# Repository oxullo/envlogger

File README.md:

# ENVLogger

Versatile hardware for logging/controlling environmental conditions.

Currently equipping:

* 2x Type-K Thermocouples EMF to digital converters
* Local Bosch-Sensortec BME680 environmental sensor
	* Temperature
	* Humidity
	* Atmospheric pressure
	* Volatile organic compounds
* 2x generic I/Os for additional 1-wire sensors (eg: DS1820B)
* 2x open-drain outputs
* 128x32, backlit FSTN LCD display
* Two buttons

## The article

Most of the information regarding this device can be found here: https://www.xul.it/blog/index.php/2020/05/16/envlogger-v1-rev-a/

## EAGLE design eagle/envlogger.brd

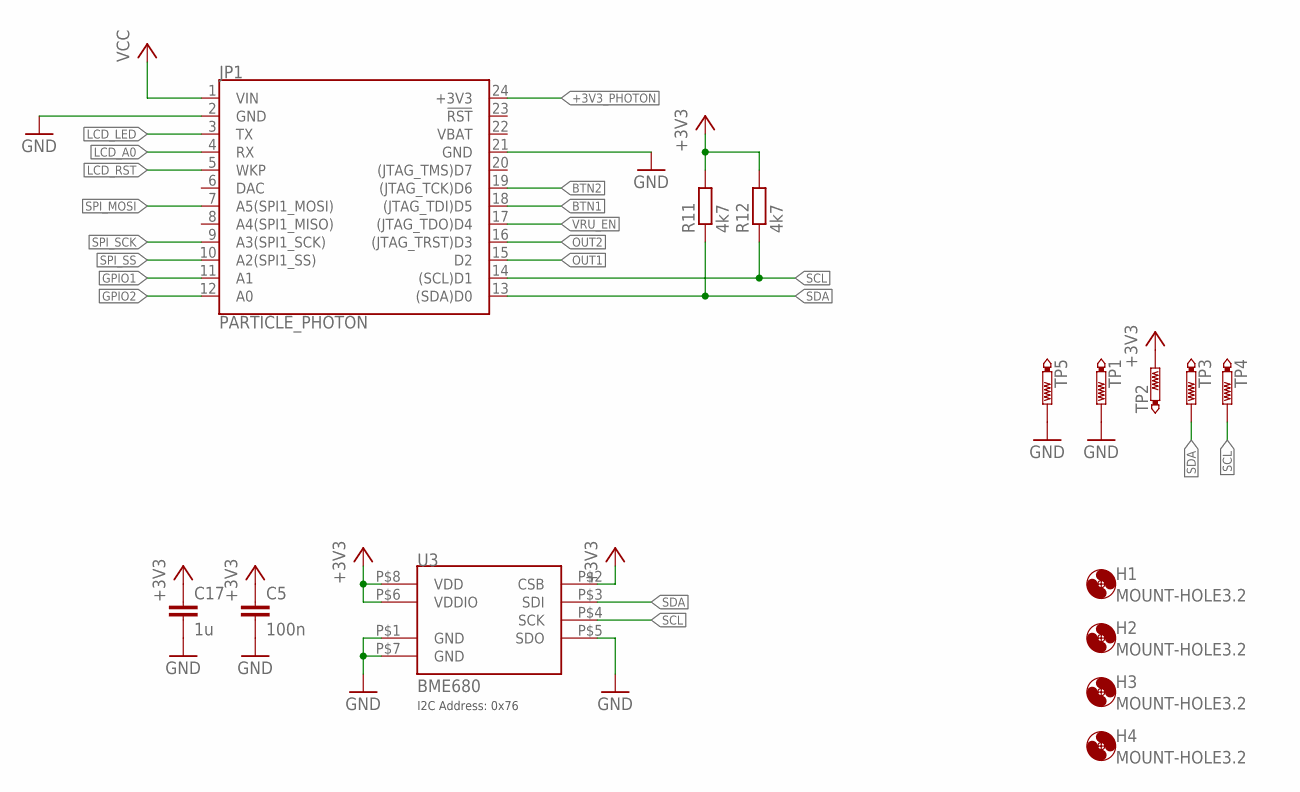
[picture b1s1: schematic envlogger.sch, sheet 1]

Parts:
C5: 100n; C0603
C17: 1u; C0603
H1, H2, H3, H4: MOUNT-HOLE3.2; 3,2
JP1: PARTICLE_PHOTON
R11, R12: 4k7; R0603
TP1, TP2, TP3, TP4: PTR1B1,27; B1,27
TP5: PTR1PAD1-13; P1-13
U3: BME680

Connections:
+3V3: C5.1, C17.1, R11.2, R12.2, TP2.TP, U3.P$2 (CSB), U3.P$6 (VDDIO), U3.P$8 (VDD); also elsewhere on the board
+3V3_PHOTON: JP1.24 (+3V3)
BTN1: JP1.18 ((JTAG_TDI)D5); also elsewhere on the board
BTN2: JP1.19 ((JTAG_TCK)D6); also elsewhere on the board
GND: C5.2, C17.2, JP1.2 (GND), JP1.21 (GND), TP1.TP, TP5.TP, U3.P$1 (GND), U3.P$5 (SDO), U3.P$7 (GND); also elsewhere on the board
GPIO1: JP1.11 (A1); also elsewhere on the board
GPIO2: JP1.12 (A0); also elsewhere on the board
LCD_A0: JP1.4 (RX); also elsewhere on the board
LCD_LED: JP1.3 (TX); also elsewhere on the board
LCD_RST: JP1.5 (WKP); also elsewhere on the board
OUT1: JP1.15 (D2); also elsewhere on the board
OUT2: JP1.16 ((JTAG_TRST)D3); also elsewhere on the board
SCL: JP1.14 ((SCL)D1), R12.1, TP4.TP, U3.P$4 (SCK); also elsewhere on the board
SDA: JP1.13 ((SDA)D0), R11.1, TP3.TP, U3.P$3 (SDI); also elsewhere on the board
SPI_MOSI: JP1.7 (A5(SPI1_MOSI)); also elsewhere on the board
SPI_SCK: JP1.9 (A3(SPI1_SCK)); also elsewhere on the board
SPI_SS: JP1.10 (A2(SPI1_SS)); also elsewhere on the board
VBAT: JP1.22 (VBAT)
VCC: JP1.1 (VIN); also elsewhere on the board
VRU_EN: JP1.17 ((JTAG_TDO)D4); also elsewhere on the board

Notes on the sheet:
I2C Address: 0x76

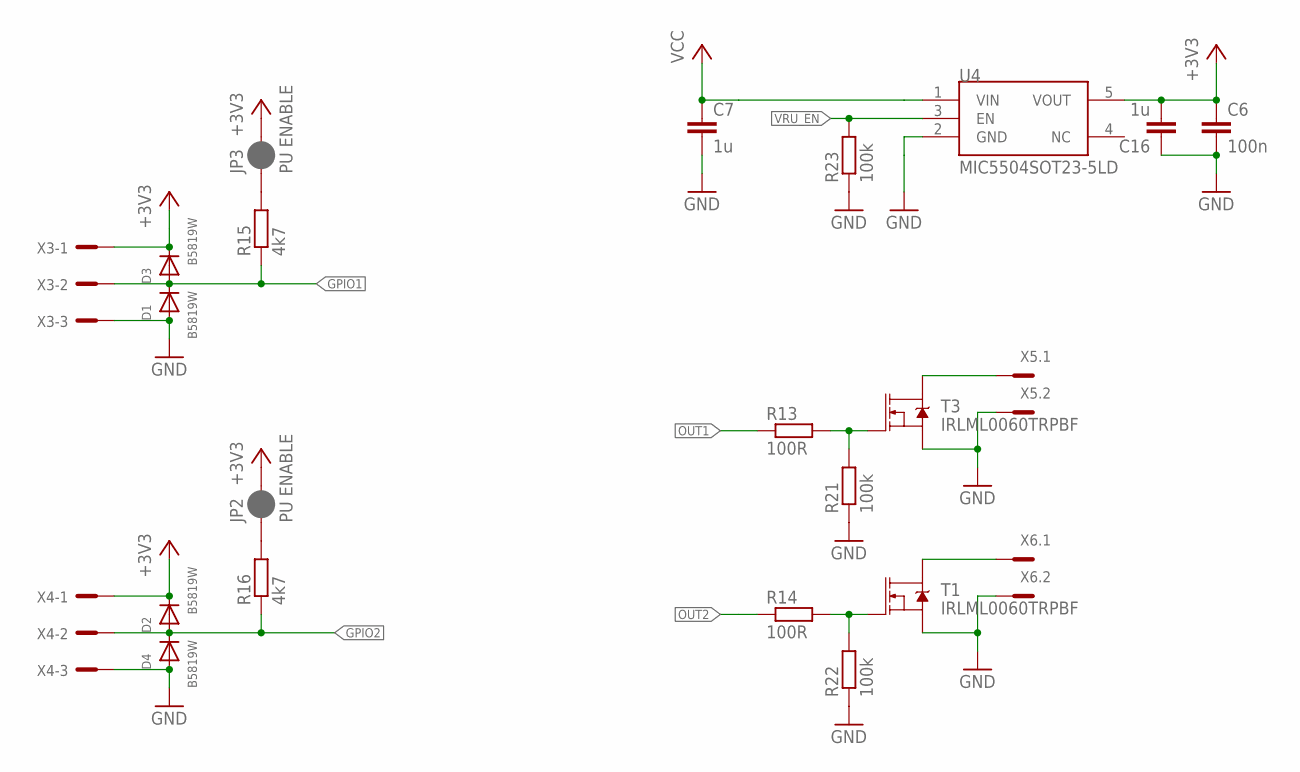
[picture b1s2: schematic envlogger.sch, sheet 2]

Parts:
C6: 100n; C0603
C7, C16: 1u; C0603
D1, D2, D3, D4: B5819W; SOD-123
JP2, JP3: PU ENABLE; SMT-JUMPER_2_NC_PASTE_SILK
R13, R14: 100R; R0603
R15, R16: 4k7; R0603
R21, R22, R23: 100k; R0603
T1, T3: IRLML0060TRPBF; SOT95P237X112-3N
U4: MIC5504SOT23-5LD; SOT95P280X145-5
X3, X4: MCV_05/3-G-2,5; MC3
X5, X6: MC2

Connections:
+3V3: C6.1, C16.2, D2.C, D3.C, JP2.2, JP3.2, U4.5 (VOUT), X3.1, X4.1; also elsewhere on the board
GND: C6.2, C7.2, C16.1, D1.A, D4.A, R21.1, R22.1, R23.1, T1.2 (S), T3.2 (S), U4.2 (GND), X3.3, X4.3, X5.2, X6.2; also elsewhere on the board
GPIO1: D1.C, D3.A, R15.1, X3.2; also elsewhere on the board
GPIO2: D2.A, D4.C, R16.1, X4.2; also elsewhere on the board
unnamed: T3.3 (D), X5.1
unnamed: R13.2, R21.2, T3.1 (G)
unnamed: T1.3 (D), X6.1
unnamed: R14.2, R22.2, T1.1 (G)
unnamed: JP2.1, R16.2
unnamed: JP3.1, R15.2
OUT1: R13.1; also elsewhere on the board
OUT2: R14.1; also elsewhere on the board
VCC: C7.1, U4.1 (VIN); also elsewhere on the board
VRU_EN: R23.2, U4.3 (EN); also elsewhere on the board

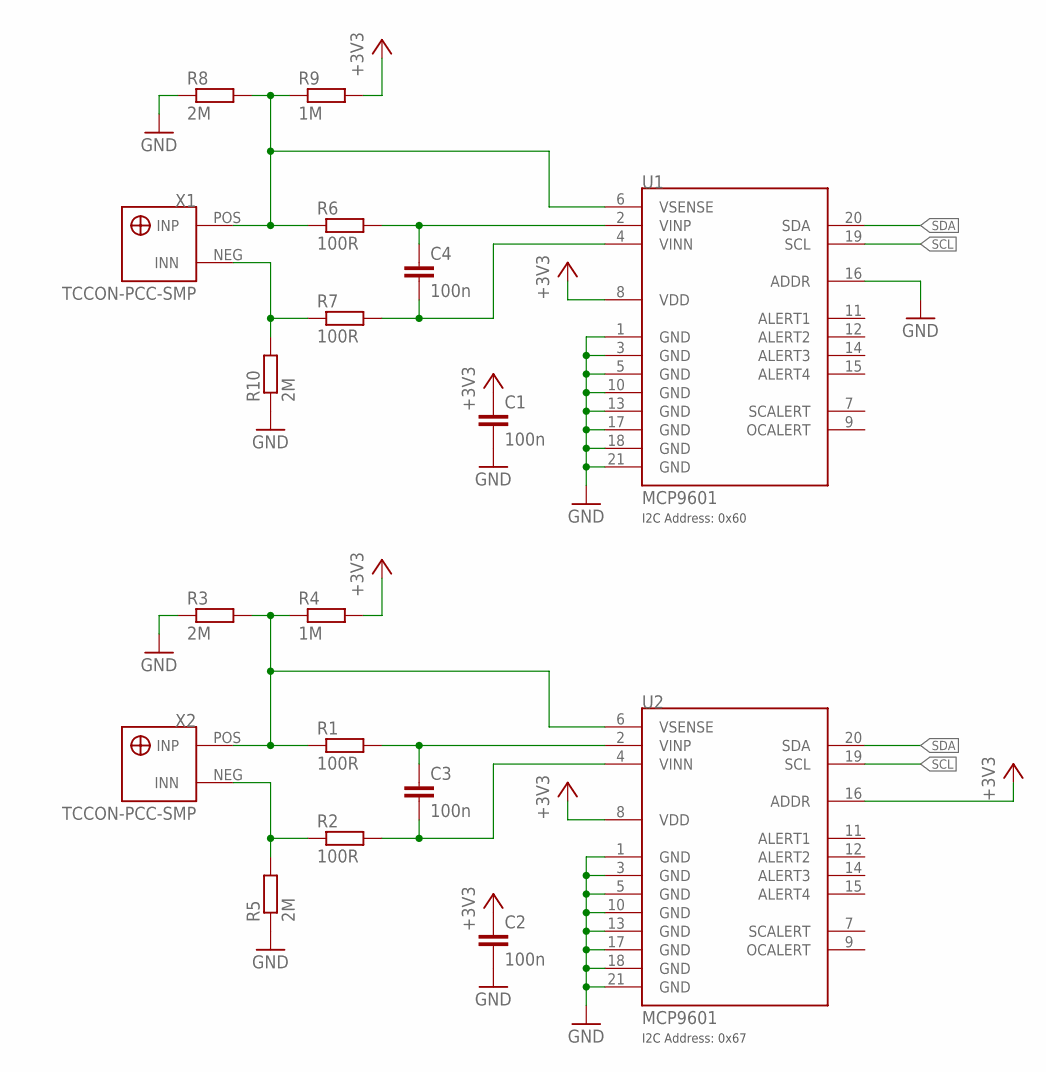
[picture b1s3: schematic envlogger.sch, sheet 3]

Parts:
C1, C2, C3, C4: 100n; C0603
R1, R2, R6, R7: 100R; R0603
R3, R5, R8, R10: 2M; R0603
R4, R9: 1M; R0603
U1, U2: MCP9601; QFN65P500X500X95-21T325N
X1, X2: TCCON-PCC-SMP

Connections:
+3V3: C1.1, C2.1, R4.2, R9.2, U1.8 (VDD), U2.8 (VDD), U2.16 (ADDR); also elsewhere on the board
GND: C1.2, C2.2, R3.1, R5.1, R8.1, R10.1, U1.1 (GND), U1.3 (GND), U1.5 (GND), U1.10 (GND), U1.13 (GND), U1.16 (ADDR), U1.17 (GND), U1.18 (GND), U1.21 (GND), U2.1 (GND), U2.3 (GND), U2.5 (GND), U2.10 (GND), U2.13 (GND), U2.17 (GND), U2.18 (GND), U2.21 (GND); also elsewhere on the board
unnamed: R1.1, R3.2, R4.1, U2.6 (VSENSE), X2.POS (INP)
unnamed: R2.1, R5.2, X2.NEG (INN)
unnamed: C3.2, R2.2, U2.4 (VINN)
unnamed: C3.1, R1.2, U2.2 (VINP)
unnamed: R6.1, R8.2, R9.1, U1.6 (VSENSE), X1.POS (INP)
unnamed: R7.1, R10.2, X1.NEG (INN)
unnamed: C4.2, R7.2, U1.4 (VINN)
unnamed: C4.1, R6.2, U1.2 (VINP)
SCL: U1.19 (SCL), U2.19 (SCL); also elsewhere on the board
SDA: U1.20 (SDA), U2.20 (SDA); also elsewhere on the board

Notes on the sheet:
I2C Address: 0x60
I2C Address: 0x67

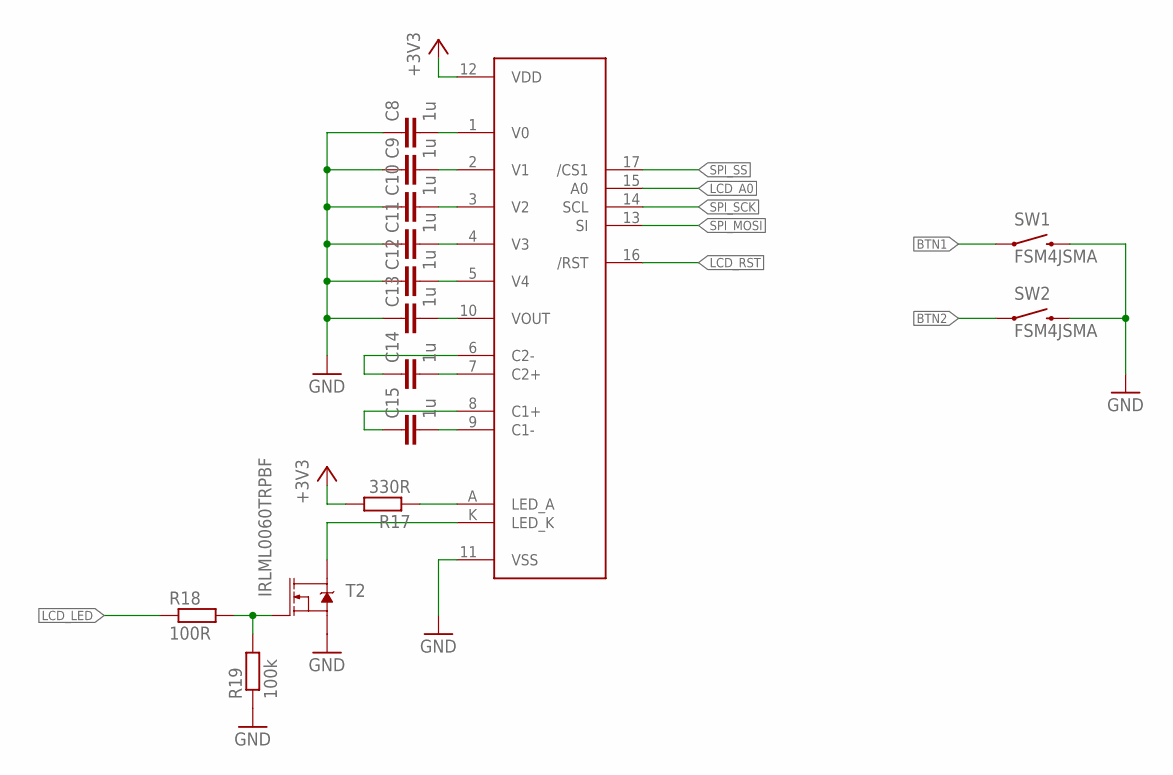
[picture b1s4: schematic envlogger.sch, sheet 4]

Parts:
C8, C9, C10, C11, C12, C13, C14, C15: 1u; C0603
DISP1: NHD-C12832A1Z
R17: 330R; R0603
R18: 100R; R0603
R19: 100k; R0603
SW1, SW2: FSM4JSMA; BUTTON-6MM-SPST
T2: IRLML0060TRPBF; SOT95P237X112-3N

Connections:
+3V3: DISP1.12 (VDD), R17.2; also elsewhere on the board
BTN1: SW1.P$1 (1); also elsewhere on the board
BTN2: SW2.P$1 (1); also elsewhere on the board
GND: C8.1, C9.1, C10.1, C11.1, C12.1, C13.1, DISP1.11 (VSS), R19.1, SW1.P$4 (2), SW2.P$4 (2), T2.2 (S); also elsewhere on the board
LCD_A0: DISP1.15 (A0); also elsewhere on the board
LCD_LED: R18.1; also elsewhere on the board
LCD_RST: DISP1.16 (/RST); also elsewhere on the board
unnamed: DISP1.A (LED_A), R17.1
unnamed: R18.2, R19.2, T2.1 (G)
unnamed: DISP1.K (LED_K), T2.3 (D)
unnamed: C8.2, DISP1.1 (V0)
unnamed: C9.2, DISP1.2 (V1)
unnamed: C10.2, DISP1.3 (V2)
unnamed: C11.2, DISP1.4 (V3)
unnamed: C12.2, DISP1.5 (V4)
unnamed: C13.2, DISP1.10 (VOUT)
unnamed: C14.2, DISP1.7 (C2+)
unnamed: C15.2, DISP1.9 (C1-)
unnamed: C14.1, DISP1.6 (C2-)
unnamed: C15.1, DISP1.8 (C1+)
SPI_MOSI: DISP1.13 (SI); also elsewhere on the board
SPI_SCK: DISP1.14 (SCL); also elsewhere on the board
SPI_SS: DISP1.17 (/CS1); also elsewhere on the board

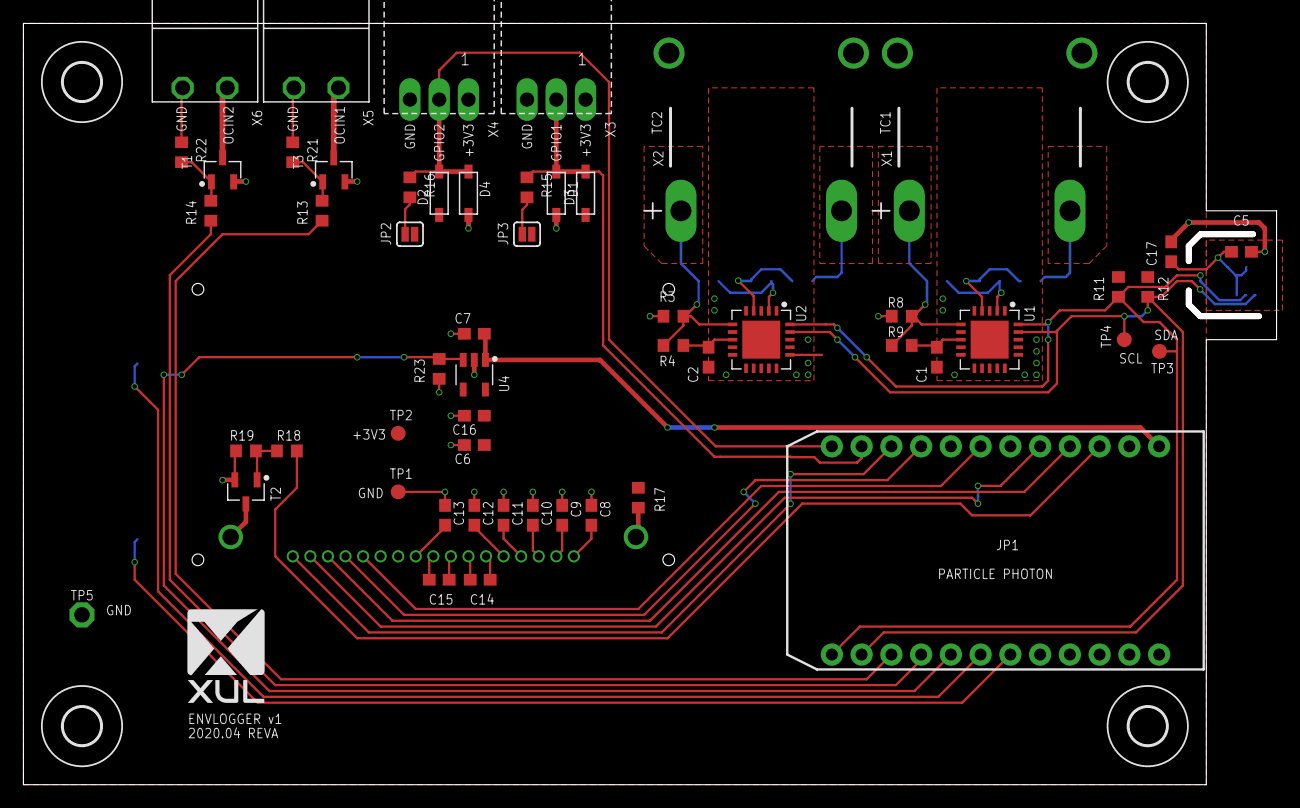
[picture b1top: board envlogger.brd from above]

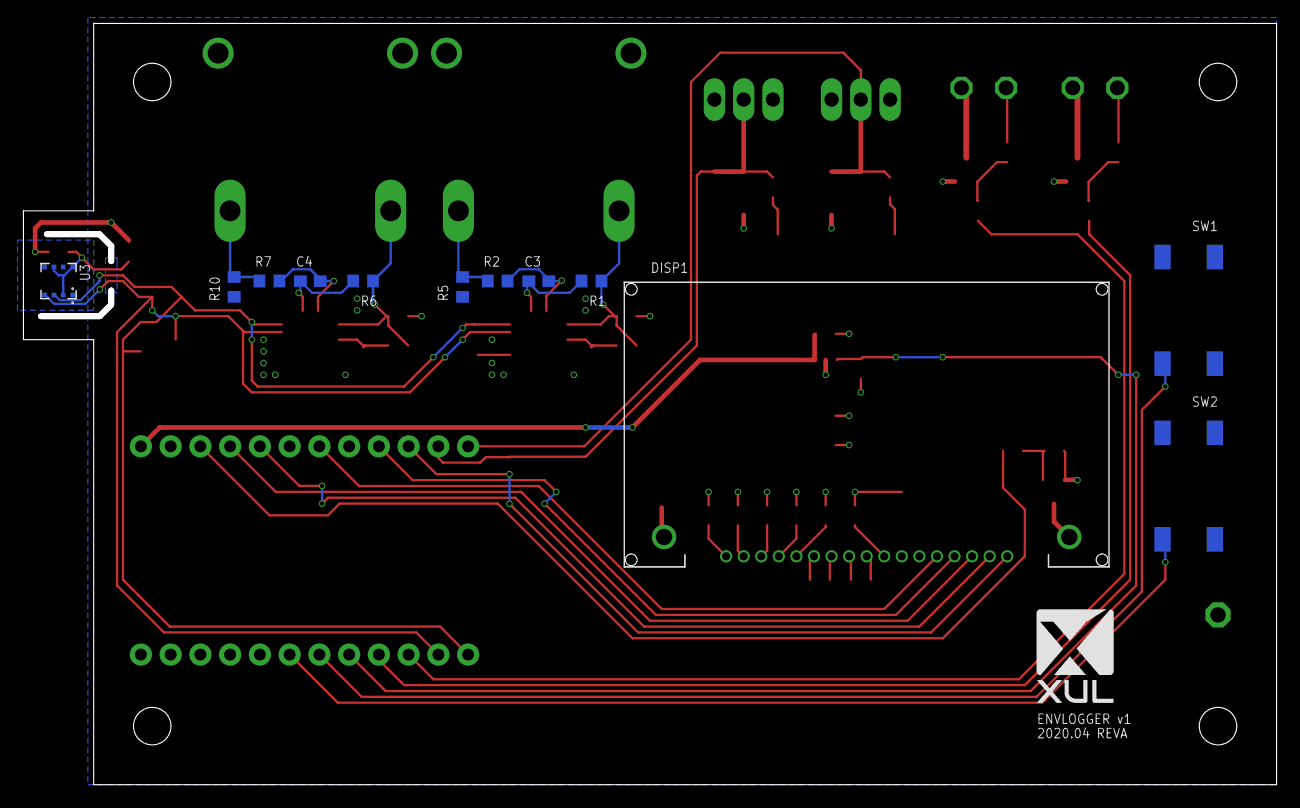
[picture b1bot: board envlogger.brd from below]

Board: 2 copper layers, 106.5 x 64.5 mm, 73 parts (13 on the bottom side), 45 nets.

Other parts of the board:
U$1, U$2: XUL-LOGO-8MMH

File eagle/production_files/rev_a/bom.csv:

"Qty";"Value";"Device";"Package";"Parts";"Description";"";
"4";"100R";"R-EU_R0603";"R0603";"R1, R2, R6, R7";"RESISTOR, European symbol";"";
"4";"100k";"R-EU_R0603";"R0603";"R19, R21, R22, R23";"RESISTOR, European symbol";"";
"6";"100n";"C-EUC0603";"C0603";"C1, C2, C3, C4, C5, C6";"CAPACITOR, European symbol";"";
"2";"1M";"R-EU_R0603";"R0603";"R4, R9";"RESISTOR, European symbol";"";
"11";"1u";"C-EUC0603";"C0603";"C7, C8, C9, C10, C11, C12, C13, C14, C15, C16, C17";"CAPACITOR, European symbol";"";
"3";"200";"R-EU_R0603";"R0603";"R13, R14, R18";"RESISTOR, European symbol";"";
"4";"2M";"R-EU_R0603";"R0603";"R3, R5, R8, R10";"RESISTOR, European symbol";"";
"1";"330R";"R-EU_R0603";"R0603";"R17";"RESISTOR, European symbol";"";
"4";"4k7";"R-EU_R0603";"R0603";"R11, R12, R15, R16";"RESISTOR, European symbol";"";
"4";"B5819W";"DIODESOD-123";"SOD-123";"D1, D2, D3, D4";"Diode";"";
"1";"BME680";"BME680";"BME680";"U3";"Environmental sensor";"";
"2";"FSM4JSMA";"FSM4JSMA";"BUTTON-6MM-SPST";"SW1, SW2";"Tactile switch SPST-NO";"";
"3";"IRLML0060TRPBF";"IRLML0060TRPBF";"SOT95P237X112-3N";"T1, T2, T3";"N-Channel MOSFET";"";
"2";"MC2";"MC2";"MC2";"X5, X6";"Mini-Combicon 3.81mm horizontal 2-polig";"";
"2";"MCP9601";"MCP9601";"QFN65P500X500X95-21T325N";"U1, U2";"Thermocouple EMF to temperature converter";"";
"2";"MCV_05/3-G-2,5";"MCV_05/3-G-2,5";"MC3";"X3, X4";"Mini-Combicon 2.50mm 3polig";"";
"1";"MIC5504SOT23-5LD";"MIC5504SOT23-5LD";"SOT95P280X145-5";"U4";"LDO 3V3 300mA";"";
"4";"MOUNT-HOLE3.2";"MOUNT-HOLE3.2";"3,2";"H1, H2, H3, H4";"MOUNTING HOLE with drill center marker";"";
"1";"NHD-C12832A1Z";"NHD-C12832A1Z";"NHD-C12832A1Z";"DISP1";"";"";
"1";"PARTICLE_PHOTON";"PARTICLE_PHOTON";"PARTICLE_PHOTON";"JP1";"Particle Photon";"";
"4";"PTR1B1,27";"PTR1B1,27";"B1,27";"TP1, TP2, TP3, TP4";"TEST PIN";"";
"1";"PTR1PAD1-13";"PTR1PAD1-13";"P1-13";"TP5";"TEST PIN";"";
"2";"PU ENABLE";"JUMPER-SMT_2_NC_PASTE_SILK";"SMT-JUMPER_2_NC_PASTE_SILK";"JP2, JP3";"Normally closed solder jumper";"";
"2";"TCCON-PCC-SMP";"TCCON-PCC-SMP";"TCCON-PCC-SMP";"X1, X2";"Thermocouple cold junction IEC miniature connector";"";

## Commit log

2020-05-16 Initial import of schematics and board layout
2020-05-16 Add production data for hardware revision A
2020-05-16 Add a hardware tester firmware
2020-05-16 Add readme
2020-05-16 Add gitignore for eagle files
2020-05-16 Add sysml and splash images
2020-05-16 Add splash image to the readme
2020-05-16 Update the sysml diagrams
2020-06-28 Proper handling of MCPs ThUPDATE and subsequent error handling, split update and dump
2020-06-28 Use the slowest filtering options for the BME680
2020-06-28 Fade off LCD backlight when inactive
2020-06-28 Initial import of a remote logger example
2020-06-28 Add a docker-compose sample configuration

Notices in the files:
parts and their libraries:
SparkFun-Boards: Licensing: Creative Commons ShareAlike 4.0 International - https://creativecommons.org/licenses/by-sa/4.0
